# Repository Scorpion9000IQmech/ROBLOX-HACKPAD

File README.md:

# ROBLOX-HACKPAD
---
This is a hackpad I have made for my gaming purposes, it could be used for anything however

it features 9 keys and a joystick meant to be moved with your thumb, it also has a little screen on the top of the macropad
it is plugged in using a usb c into the xiao rp2040 on the top right of the case, you can of course change what the keys and joystick do
the screen is plugged into the connectors, and the same goes for the joystick

### Schematic
---

### PCB LAYOUT
---

### CASE FOR PBC
---

# BOM
---
| Item | Price | source |
|---|---|---|
| PCB | 8.1 USD | Plus shipping(JLPCB) |
| XiaoRP2040 | 5.93 USD | [Ali Express](https://a.aliexpress.com/_c4q1RiOr) |
| Keyboard switches | 10.4 USD | [Ali Express](https://a.aliexpress.com/_c4oDU77V) |
| 0.91 OLED | 2.91 USD | [Ali Express](https://a.aliexpress.com/_c4tRPQxp) |
| HW-504 joystick | 7.8 USD | [Ali Express](https://a.aliexpress.com/_c3pqUAtd) |

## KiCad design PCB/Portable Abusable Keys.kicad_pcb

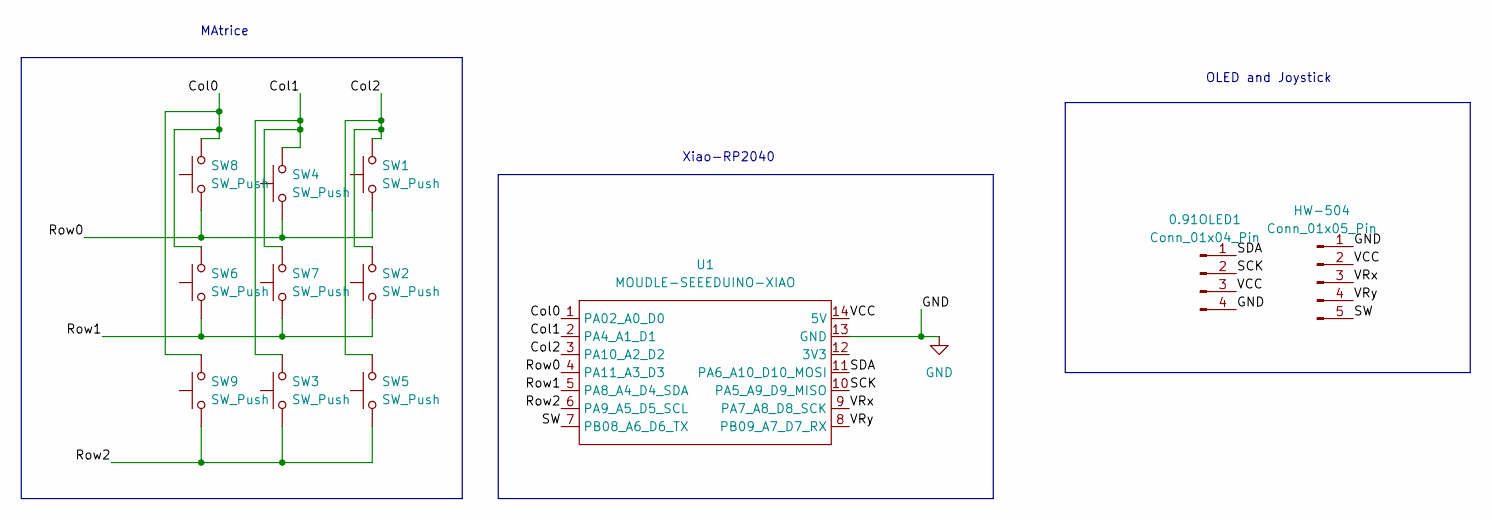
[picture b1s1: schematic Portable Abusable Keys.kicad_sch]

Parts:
0.91OLED1: Conn_01x04_Pin; PinHeader_1x04_P2.54mm_Vertical
HW-504: Conn_01x05_Pin; PinHeader_1x05_P2.54mm_Vertical
SW1, SW2, SW3, SW4, SW5, SW6, SW7, SW8, SW9: SW_Push; SW_Cherry_MX_1.00u_PCB
U1: MOUDLE-SEEEDUINO-XIAO; XIAO-Generic-Hybrid-14P-2.54-21X17.8MM

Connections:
/Col0: SW6.2, SW8.2, SW9.2, U1.1 (PA02_A0_D0)
/Col1: SW3.2, SW4.2, SW7.2, U1.2 (PA4_A1_D1)
/Col2: SW1.2, SW2.2, SW5.2, U1.3 (PA10_A2_D2)
/Row0: SW1.1, SW4.1, SW8.1, U1.4 (PA11_A3_D3)
/Row1: SW2.1, SW6.1, SW7.1, U1.5 (PA8_A4_D4_SDA)
/Row2: SW3.1, SW5.1, SW9.1, U1.6 (PA9_A5_D5_SCL)
/SCK: 0.91OLED1.2, U1.10 (PA5_A9_D9_MISO)
/SDA: 0.91OLED1.1, U1.11 (PA6_A10_D10_MOSI)
/SW: HW-504.5, U1.7 (PB08_A6_D6_TX)
/VCC: 0.91OLED1.3, HW-504.2, U1.14 (5V)
/VRx: HW-504.3, U1.9 (PA7_A8_D8_SCK)
/VRy: HW-504.4, U1.8 (PB09_A7_D7_RX)
GND: 0.91OLED1.4, HW-504.1, U1.13 (GND)

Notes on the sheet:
MAtrice
OLED and Joystick
Xiao-RP2040

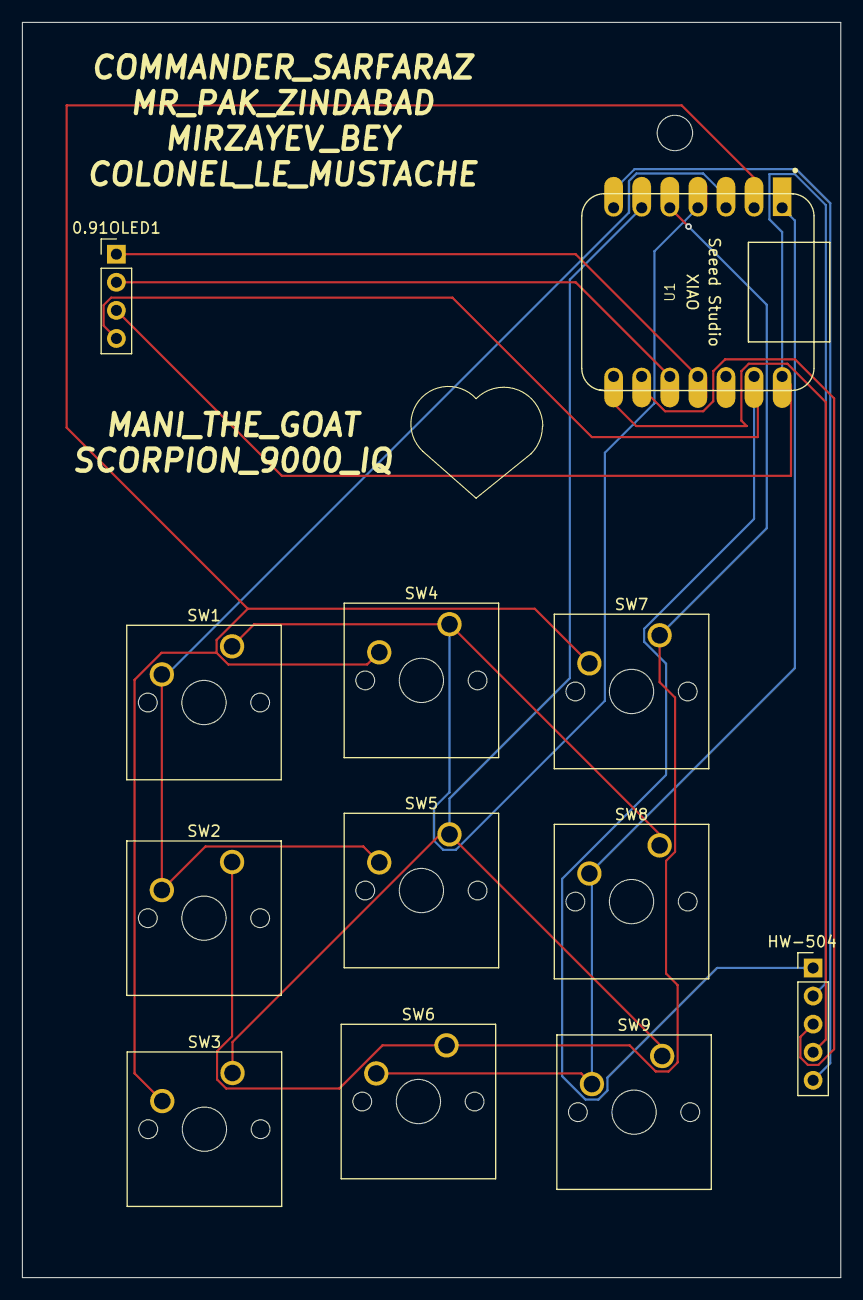
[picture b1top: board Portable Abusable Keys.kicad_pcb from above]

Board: 2 copper layers, 74.0 x 113.5 mm, 12 parts (0 on the bottom side), 13 nets.
